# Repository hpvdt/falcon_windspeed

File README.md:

# Windspeed System

System to determine the relative wind to the aircraft as a 3D vector using an array of differential pressure sensors.

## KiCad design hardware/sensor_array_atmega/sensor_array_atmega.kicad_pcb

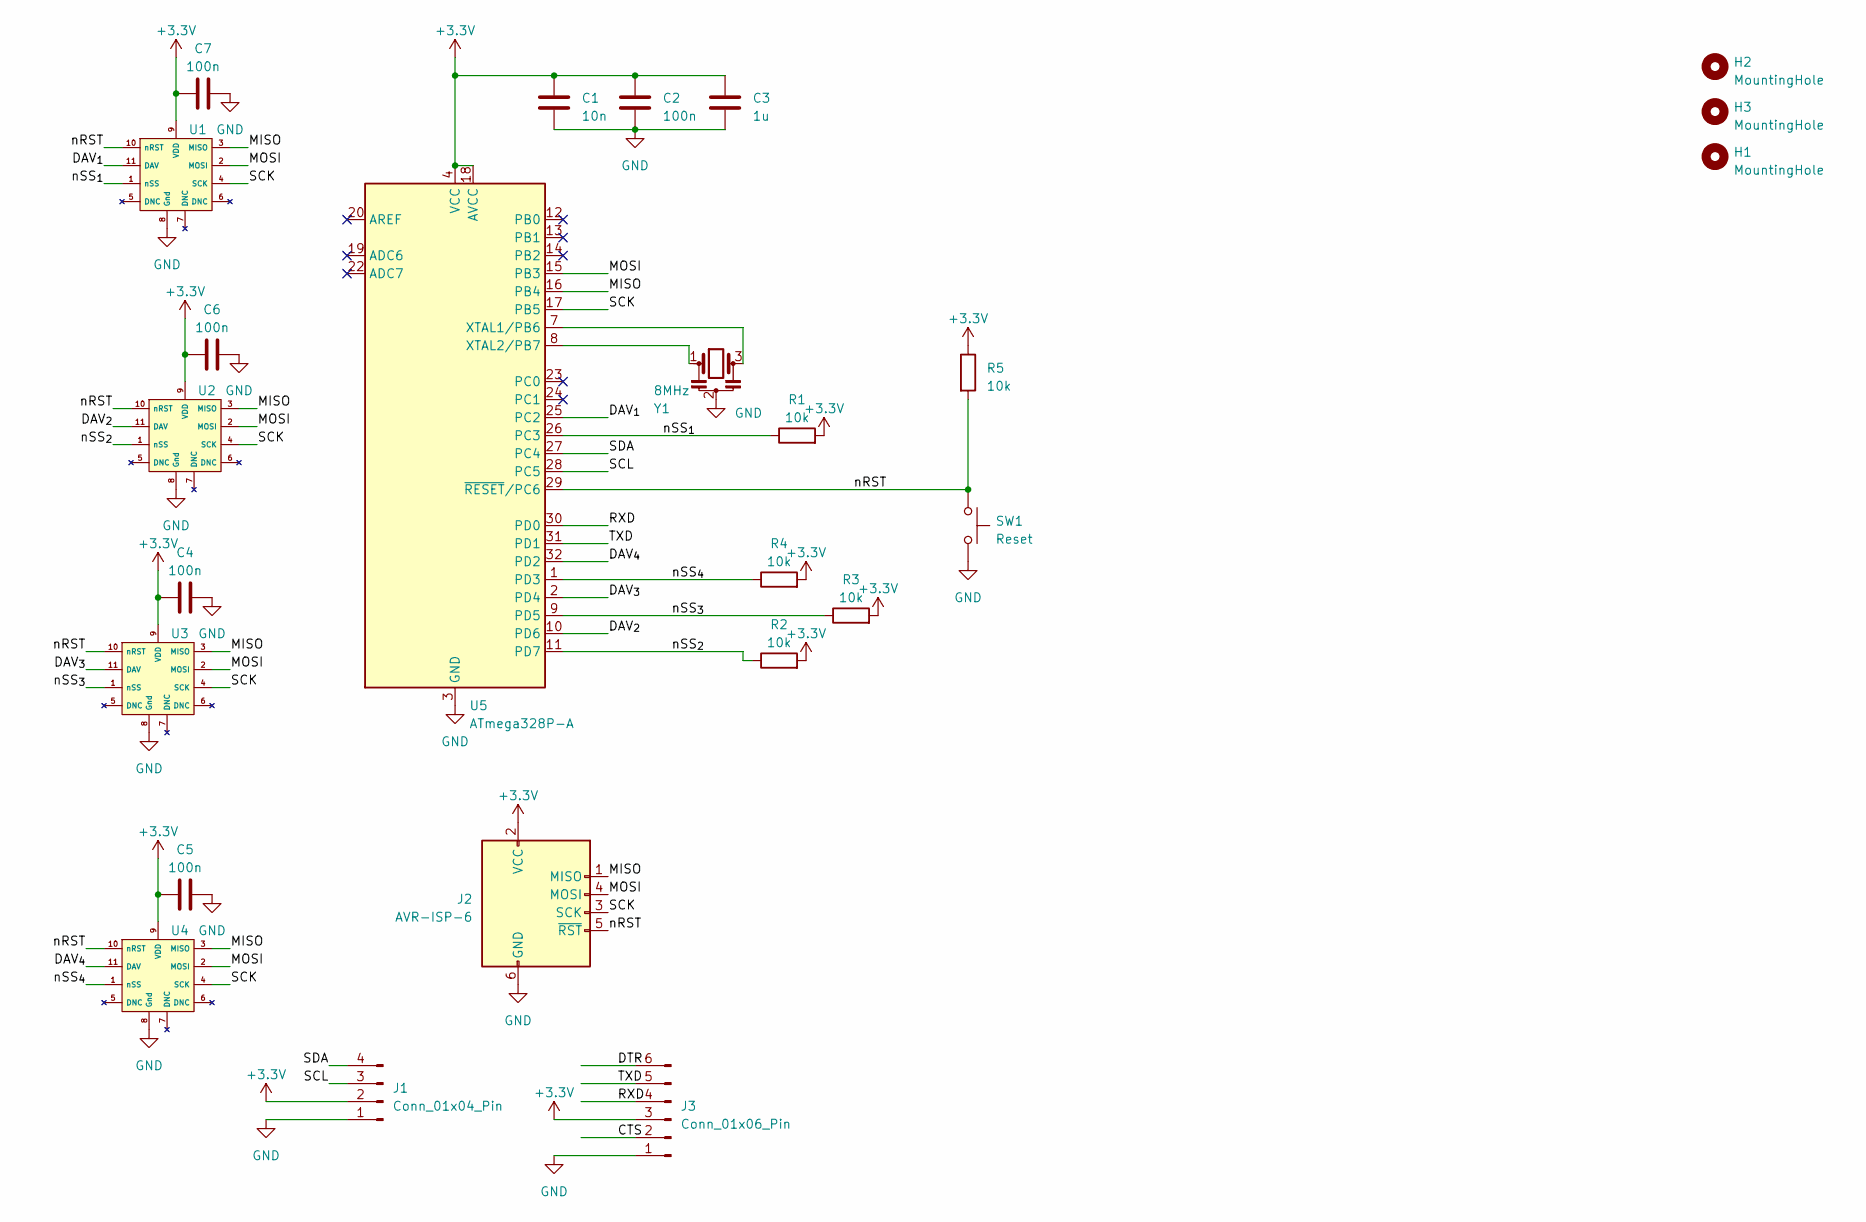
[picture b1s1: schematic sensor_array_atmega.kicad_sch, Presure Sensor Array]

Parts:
C1: 10n; C_0603_1608Metric
C2, C4, C5, C6, C7: 100n; C_0603_1608Metric
C3: 1u; C_0603_1608Metric
H1, H2, H3: MountingHole; MountingHole_3.2mm_M3
J1: Conn_01x04_Pin; PinHeader_1x04_P2.54mm_Vertical
J2: AVR-ISP-6; IDC-Header_2x03_P2.54mm_Vertical_SMD
J3: Conn_01x06_Pin; PinHeader_1x06_P2.54mm_Vertical
R1, R2, R3, R4, R5: 10k; R_0603_1608Metric
SW1: Reset; SW_SPST_SKQG_WithStem
U1, U2, U3, U4: HV120SM02C
U5: ATmega328P-A; TQFP-32_7x7mm_P0.8mm
Y1: 8MHz; Resonator_SMD-3Pin_7.2x3.0mm_HandSoldering

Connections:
+3.3V: C1.1, C2.1, C3.1, C4.1, C5.1, C6.1, C7.1, J1.2, J2.2 (VCC), J3.3, R1.2, R2.2, R3.2, R4.2, R5.1, U1.9 (VDD), U2.9 (VDD), U3.9 (VDD), U4.9 (VDD), U5.4 (VCC), U5.6 (VCC), U5.18 (AVCC)
/CTS: J3.2
/DAV_{1}: U1.11 (DAV), U5.25 (PC2)
/DAV_{2}: U2.11 (DAV), U5.10 (PD6)
/DAV_{3}: U3.11 (DAV), U5.2 (PD4)
/DAV_{4}: U4.11 (DAV), U5.32 (PD2)
/DTR: J3.6
/MISO: J2.1 (MISO), U1.3 (MISO), U2.3 (MISO), U3.3 (MISO), U4.3 (MISO), U5.16 (PB4)
/MOSI: J2.4 (MOSI), U1.2 (MOSI), U2.2 (MOSI), U3.2 (MOSI), U4.2 (MOSI), U5.15 (PB3)
/RXD: J3.4, U5.30 (PD0)
/SCK: J2.3 (SCK), U1.4 (SCK), U2.4 (SCK), U3.4 (SCK), U4.4 (SCK), U5.17 (PB5)
/SCL: J1.3, U5.28 (PC5)
/SDA: J1.4, U5.27 (PC4)
/TXD: J3.5, U5.31 (PD1)
/nRST: J2.5 (~RST), R5.2, SW1.1, U1.10 (nRST), U2.10 (nRST), U3.10 (nRST), U4.10 (nRST), U5.29 (~RESET/PC6)
/nSS_{1}: R1.1, U1.1 (nSS), U5.26 (PC3)
/nSS_{2}: R2.1, U2.1 (nSS), U5.11 (PD7)
/nSS_{3}: R3.1, U3.1 (nSS), U5.9 (PD5)
/nSS_{4}: R4.1, U4.1 (nSS), U5.1 (PD3)
GND: C1.2, C2.2, C3.2, C4.2, C5.2, C6.2, C7.2, J1.1, J2.6 (GND), J3.1, SW1.2, U1.8 (Gnd), U2.8 (Gnd), U3.8 (Gnd), U4.8 (Gnd), U5.3 (GND), U5.5 (GND), U5.21 (GND), Y1.2
unnamed: U5.7 (XTAL1/PB6), Y1.3
unnamed: U5.8 (XTAL2/PB7), Y1.1

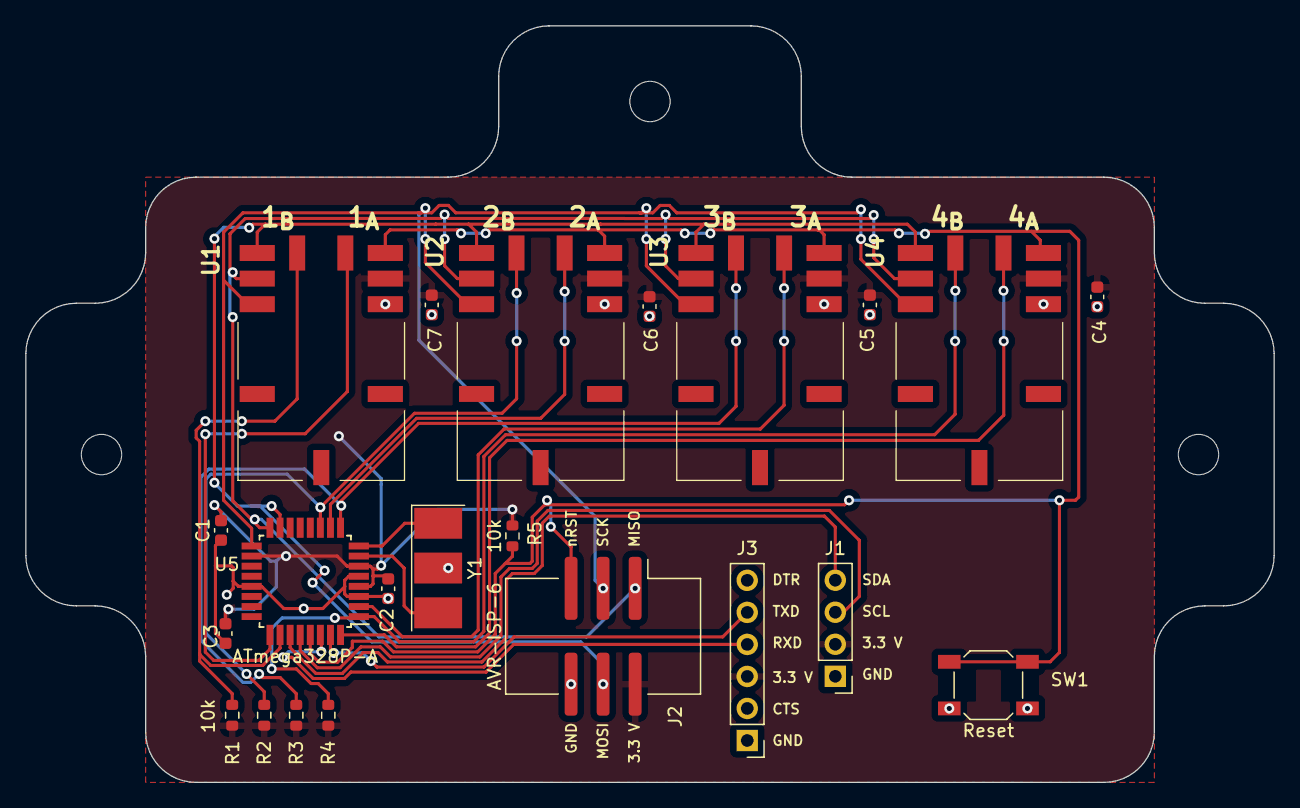
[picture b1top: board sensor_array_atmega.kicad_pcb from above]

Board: 2 copper layers, 99.0 x 60.0 mm, 25 parts (0 on the bottom side), 20 nets.

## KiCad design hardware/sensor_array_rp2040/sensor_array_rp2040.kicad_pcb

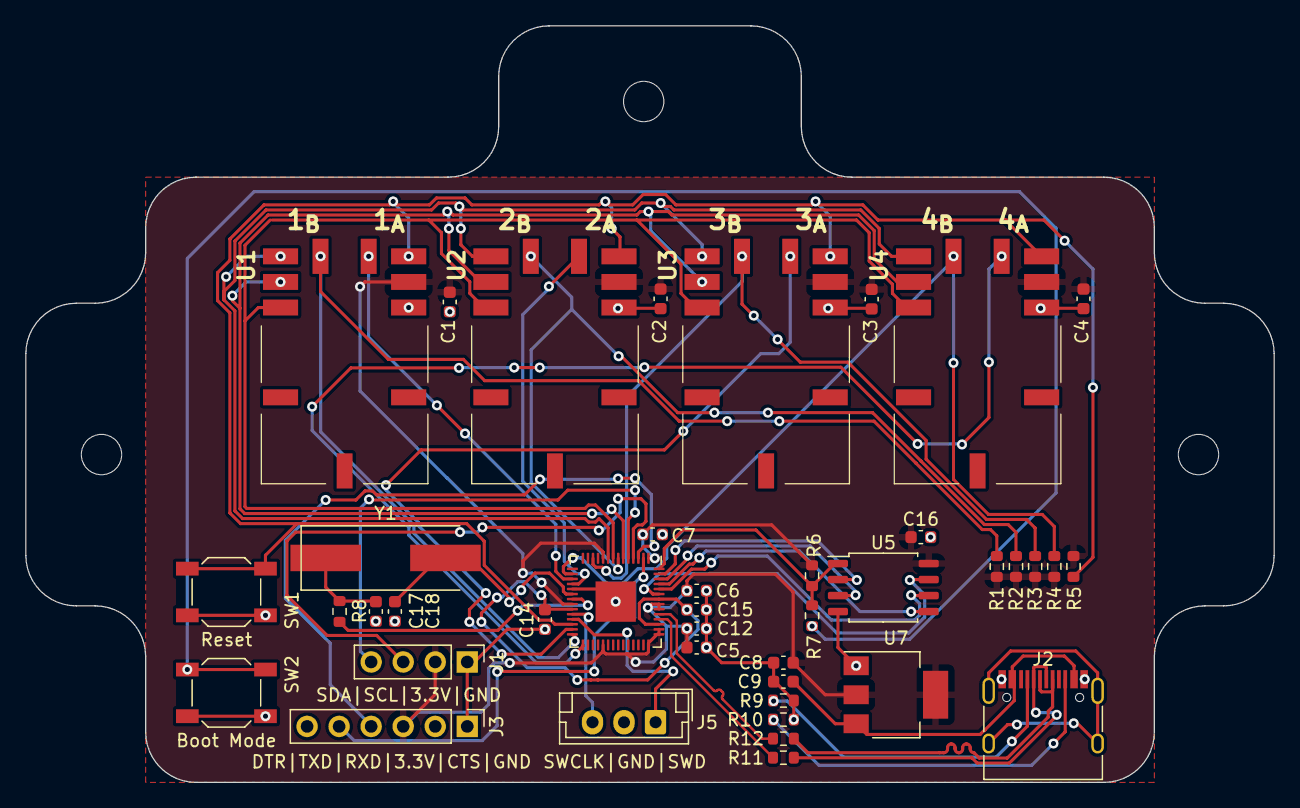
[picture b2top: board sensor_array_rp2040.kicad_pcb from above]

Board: 2 copper layers, 99.0 x 60.0 mm, 44 parts (0 on the bottom side), 38 nets.

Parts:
C1, C2, C3, C4, C5, C6, C7, C14, C16: 100n; C_0603_1608Metric
C8, C9: 22u; C_0603_1608Metric
C12, C15: 1n; C_0603_1608Metric
C17, C18: 27p; C_0603_1608Metric
H1, H2, H3: MountingHole; MountingHole_3.2mm_M3
J1: Conn_01x04_Pin; PinHeader_1x04_P2.54mm_Vertical
J2: USB_C_Receptacle_USB2.0; USB_C_Receptacle_HRO_TYPE-C-31-M-12
J3: Conn_01x06_Pin; PinHeader_1x06_P2.54mm_Vertical
J5: Conn_01x03_Pin; JST_EH_B3B-EH-A_1x03_P2.50mm_Vertical
R1, R2, R3, R4, R5, R6: 10k; R_0603_1608Metric
R7, R8: 1k; R_0603_1608Metric
R9, R10: 5.1k; R_0603_1608Metric
R11, R12: 22; R_0603_1608Metric
SW1: Reset; SW_SPST_SKQG_WithStem
SW2: Boot Mode; SW_SPST_SKQG_WithStem
U1, U2, U3, U4: HV120SM02C
U5: W25Q128JVS; SOIC-8_5.23x5.23mm_P1.27mm
U6: RP2040; QFN-56-1EP_7x7mm_P0.4mm_EP3.2x3.2mm
U7: AZ1117-3.3; SOT-223-3_TabPin2
Y1: Crystal; Crystal_SMD_HC49-SD(ABLS-12.000MHZ-B4-T)

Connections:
+1V1: C14.1, C15.1, U6.23 (DVDD), U6.45 (VREG_VOUT), U6.50 (DVDD)
+3.3V: C1.1, C2.1, C3.1, C4.1, C5.1, C6.1, C7.1, C8.2, C12.1, C16.1, J1.2, J3.3, R1.2, R2.2, R3.2, R4.2, R5.1, R6.1, U1.9 (VDD), U2.9 (VDD), U3.9 (VDD), U4.9 (VDD), U5.8 (VCC), U6.1 (IOVDD), U6.10 (IOVDD), U6.22 (IOVDD), U6.33 (IOVDD), U6.42 (IOVDD), U6.43 (ADC_AVDD), U6.44 (VREG_IN), U6.48 (USB_VDD), U6.49 (IOVDD), U7.2 (VO)
+5V: C9.2, J2.A4 (VBUS), J2.A9 (VBUS), J2.B4 (VBUS), J2.B9 (VBUS), U7.3 (VI)
/D+: J2.A6 (D+), J2.B6 (D+), R12.1
/D-: J2.A7 (D-), J2.B7 (D-), R11.1
/DAV_{1}: U1.11 (DAV), U6.17 (GPIO14)
/DAV_{2}: U2.11 (DAV), U6.18 (GPIO15)
/DAV_{3}: U3.11 (DAV), U6.27 (GPIO16)
/DAV_{4}: U4.11 (DAV), U6.29 (GPIO18)
/MISO: U1.3 (MISO), U2.3 (MISO), U3.3 (MISO), U4.3 (MISO), U6.6 (GPIO4)
/MOSI: U1.2 (MOSI), U2.2 (MOSI), U3.2 (MOSI), U4.2 (MOSI), U6.9 (GPIO7)
/QSPI_SCLK: U5.6 (CLK), U6.52 (QSPI_SCLK)
/QSPI_SD0: U5.5 (DI(IO0)), U6.53 (QSPI_SD0)
/QSPI_SD1: U5.2 (DO(IO1)), U6.55 (QSPI_SD1)
/QSPI_SD2: U5.3 (IO2), U6.54 (QSPI_SD2)
/QSPI_SD3: U5.7 (IO3), U6.51 (QSPI_SD3)
/QSPI_SS: R6.2, R7.1, U5.1 (~CS), U6.56 (QSPI_SS)
/RXD: J3.4, U6.3 (GPIO1)
/SCK: U1.4 (SCK), U2.4 (SCK), U3.4 (SCK), U4.4 (SCK), U6.8 (GPIO6)
/SCL: J1.4, U6.5 (GPIO3)
/SDA: J1.3, U6.4 (GPIO2)
/SWCLK: J5.3, U6.24 (SWCLK)
/SWD: J5.1, U6.25 (SWD)
/TXD: J3.5, U6.2 (GPIO0)
/USB_BOOT: R7.2, SW2.2
/USB_D+: R12.2, U6.47 (USB_DP)
/USB_D-: R11.2, U6.46 (USB_DM)
/nRST: R5.2, SW1.2, U1.10 (nRST), U2.10 (nRST), U3.10 (nRST), U4.10 (nRST), U6.26 (RUN)
/nSS_{1}: R1.1, U1.1 (nSS), U6.28 (GPIO17)
/nSS_{2}: R2.1, U2.1 (nSS), U6.7 (GPIO5)
/nSS_{3}: R3.1, U3.1 (nSS), U6.12 (GPIO9)
/nSS_{4}: R4.1, U4.1 (nSS), U6.16 (GPIO13)
GND: C1.2, C2.2, C3.2, C4.2, C5.2, C6.2, C7.2, C8.1, C9.1, C12.2, C14.2, C15.2, C16.2, C17.1, C18.1, J1.1, J2.A1 (GND), J2.A12 (GND), J2.B1 (GND), J2.B12 (GND), J3.1, J5.2, R9.2, R10.2, SW1.1, SW2.1, U1.8 (GND), U2.8 (GND), U3.8 (GND), U4.8 (GND), U5.4 (GND), U6.19 (TESTEN), U6.57 (GND), U7.1 (GND)
unnamed: C17.2, R8.1, Y1.1
unnamed: J2.A5 (CC1), R9.1
unnamed: J2.B5 (CC2), R10.1
unnamed: C18.2, U6.20 (XIN), Y1.2
unnamed: R8.2, U6.21 (XOUT)

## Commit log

2023-11-30 pressure sensor code upload
    test?
2023-11-30 Example ND005D Library
    Gift from Savo
2023-12-01 upload platformio project
2023-12-01 Minor addons
2023-12-01 Update nd005.cpp
    Corrected MISO/MOSI pin allocations
2023-12-01 Cleared .vscode
2023-12-01 Changes needed for proper upload anbd upload
2023-12-01 Added delays needed for ND005D
2023-12-01 Oopsie, added the constant for pause
2023-12-02 Test for all sensors
2024-01-17 Upload of code
    having issues with just about everything
2024-01-17 Ignoring OS files
2024-01-17 Fixed up `PressureSensor` class
    - Removed unneeded `static` qualifier for `private` variables
    - Moved `pressureSPI` to be global instead of a private object. Makes more sense for all sensors to share this object and it fixes some issues.
2024-01-17 Changed main code to use objects
2024-02-09 fixed errors, added spi bus pointer
2024-02-09 Fixed redundant things in previous merge
2024-02-09 moved shiet to hpp and cpp files
2024-02-10 Moved ND005 constants into `cpp` file
2024-02-10 Tracking active pressure range in ND005 class
2024-02-10 Updated ND005 initialization
2024-02-23 add function to convert rawreading to pressureval
2024-03-08 adjusted defult range from 5.0 to 0.5
2024-03-09 added "buildVector" function
2024-03-12 added windSpeed function
2024-03-12 made some changes to windSpeed
2024-03-13 more windSpeed changes
2024-03-13 windSpeed works, but needs more test/verification
2024-03-13 altered data display
2024-03-13 altered data display 2
2024-03-23 added windSpeedValue = ||windSpeedVector||
2024-04-11 new reading to pressure; pressure to speed funcs
2024-04-12 wrote conversion functions
2024-04-12 minor formatting adjustments
2024-04-13 minor formatting changes
2024-04-13 adjusted function and variable names for clarity
2024-04-13 changed more names for clarity
2024-04-13 added some comments
2024-04-13 fixed nan/inf/0.0 problem (sqrt(-x)), very small #
2024-07-01 Fixed inversion for `absolute` to use float constant
2024-07-01 Making pressure units explicit
2024-07-06 Merged pressure conversion functions
    Pressure conversion functions were originally seperate
    to the helper functions which made use of the values.
    This led to issues regarding unit mismatches. So now
    pressure readings have their units specified and
    wind speed function collects pressure directly.
2024-07-17 Baseline I2C communication functions working
2024-08-08 Replaced `absolute()` with `fabsf()`
2024-08-08 Added discrete `readRawPressure` function
2024-08-12 Moved to use `printf()` for cleaner code and message
2024-08-12 Restored sign to wind speed result
2024-08-12 Properly updating ctrol register on chips
2024-08-12 Added function to try and automatically zero sensors
2024-08-12 Fixed angular math for wind vector
2024-08-12 Precalculating axis projection factors
2024-08-16 Added additional configuration functions
2024-08-16 Enum for bandwidth
2024-08-16 Fixed raw reading
    Using `static` to store the last reading, resulted in it being shared
    between all objects of a class which was far from ideal. Moved it to be
    a private attribute of the class.
2025-08-17 Reorganized and added hardware projects
